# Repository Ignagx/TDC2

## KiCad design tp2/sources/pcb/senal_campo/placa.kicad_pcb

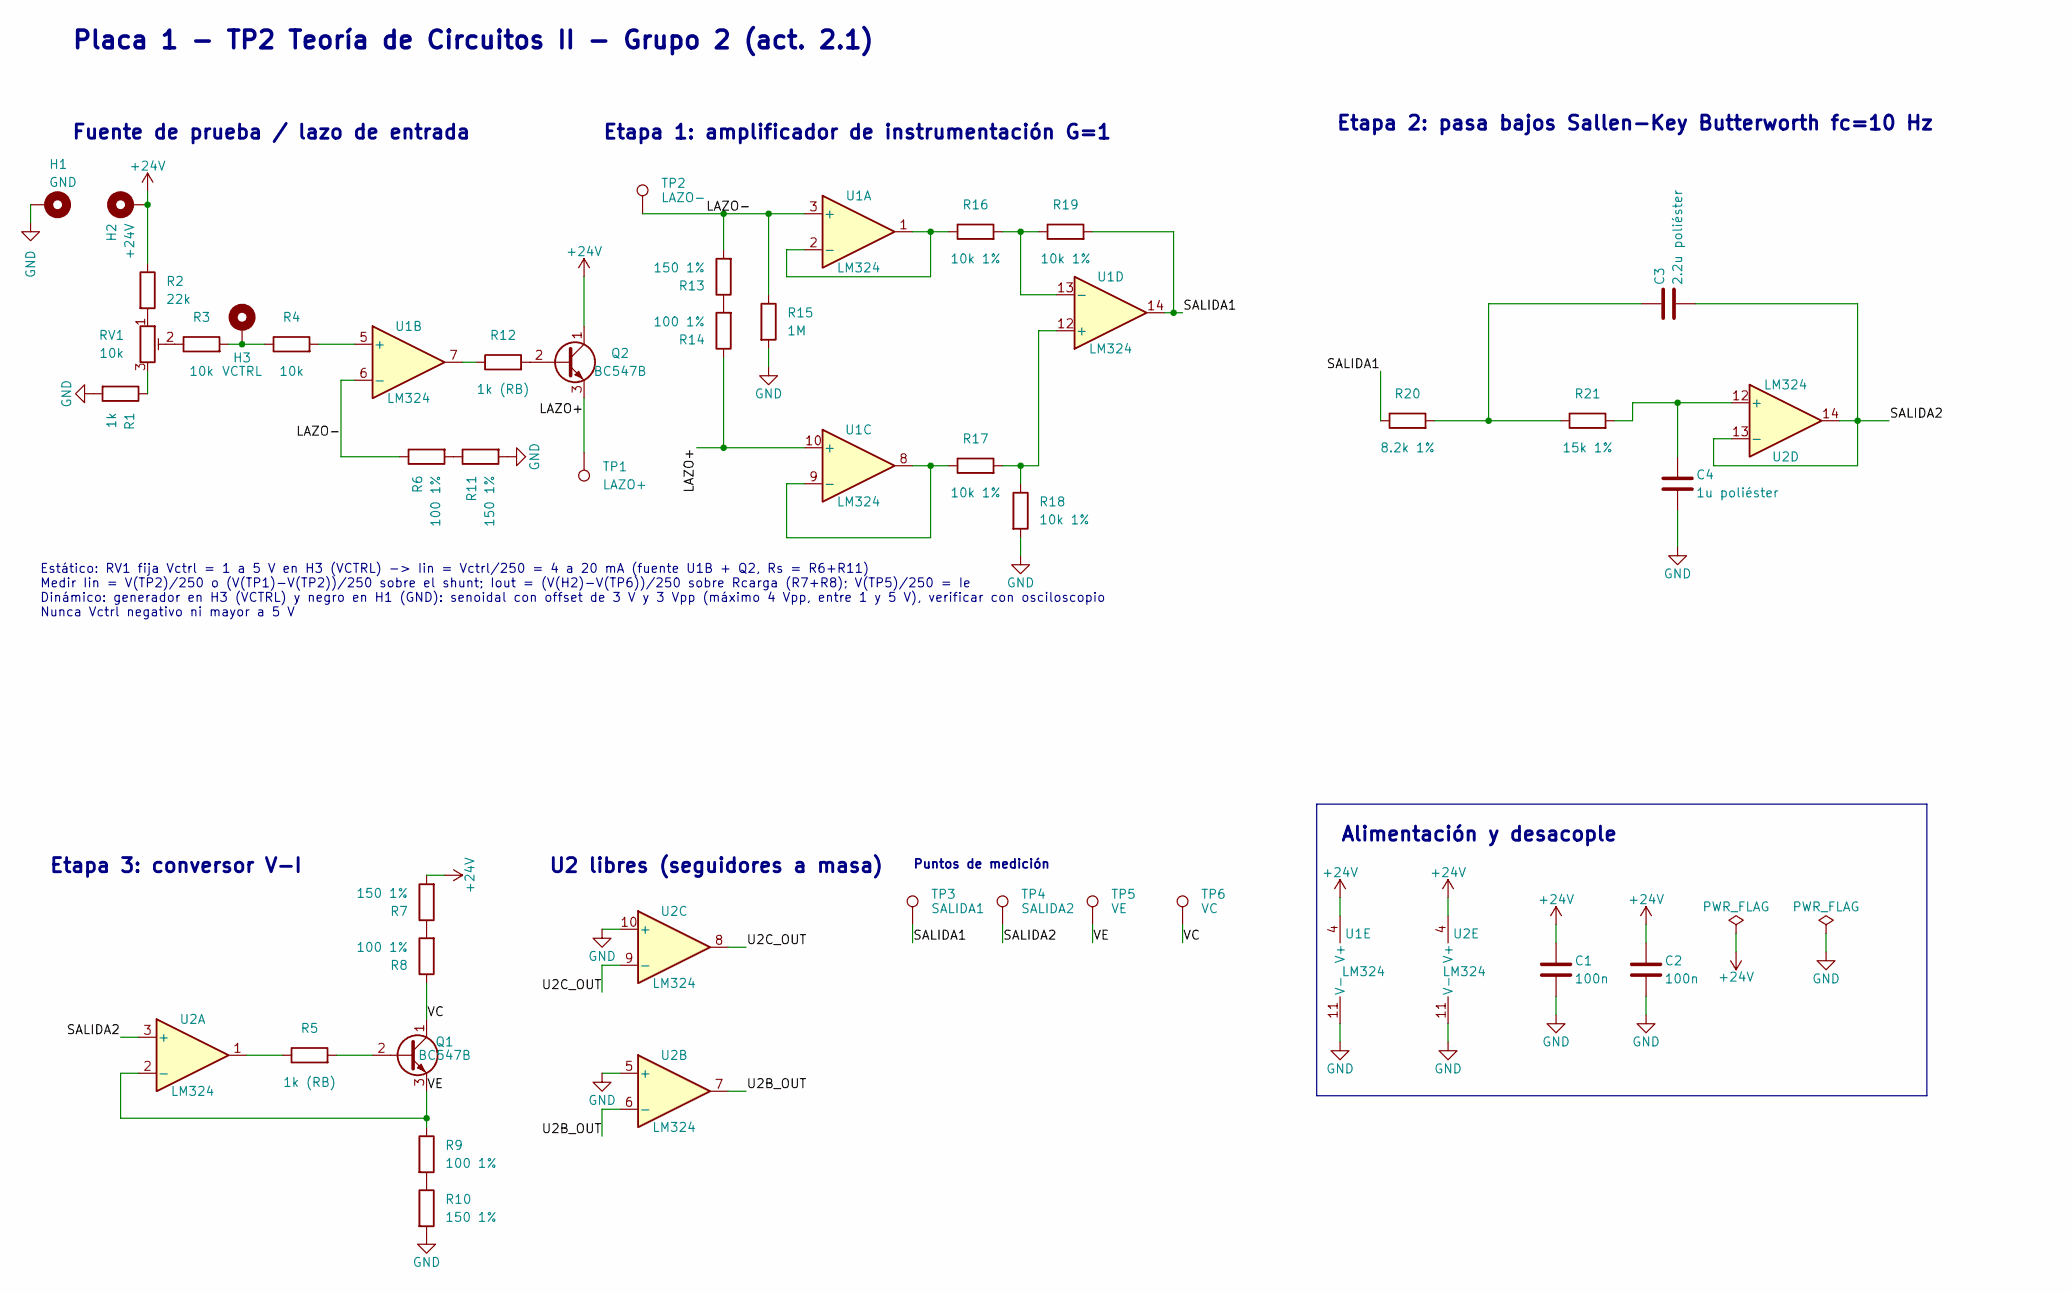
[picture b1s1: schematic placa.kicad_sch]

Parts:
C1, C2: 100n; C_Disc_D5.0mm_W2.5mm_P5.00mm
C3: 2.2u poliéster; C_Rect_L26.5mm_W10.5mm_P22.50mm_MKS4
C4: 1u poliéster; C_Rect_L7.2mm_W5.5mm_P5.00mm_FKS2_FKP2_MKS2_MKP2
H1: GND; Pad_Cocodrilo_6x8mm
H2: +24V; Pad_Cocodrilo_6x8mm
H3: VCTRL; Pad_Cocodrilo_6x8mm
Q1, Q2: BC547B; TO-92_Inline_Wide
R1: 1k; R_Axial_DIN0207_L6.3mm_D2.5mm_P10.16mm_Horizontal
R2: 22k; R_Axial_DIN0207_L6.3mm_D2.5mm_P10.16mm_Horizontal
R3, R4: 10k; R_Axial_DIN0207_L6.3mm_D2.5mm_P10.16mm_Horizontal
R5, R12: 1k (RB); R_Axial_DIN0207_L6.3mm_D2.5mm_P10.16mm_Horizontal
R6, R8, R9, R14: 100 1%; R_Axial_DIN0207_L6.3mm_D2.5mm_P10.16mm_Horizontal
R7, R10, R11, R13: 150 1%; R_Axial_DIN0207_L6.3mm_D2.5mm_P10.16mm_Horizontal
R15: 1M; R_Axial_DIN0207_L6.3mm_D2.5mm_P10.16mm_Horizontal
R16, R17, R18, R19: 10k 1%; R_Axial_DIN0207_L6.3mm_D2.5mm_P10.16mm_Horizontal
R20: 8.2k 1%; R_Axial_DIN0207_L6.3mm_D2.5mm_P10.16mm_Horizontal
R21: 15k 1%; R_Axial_DIN0207_L6.3mm_D2.5mm_P10.16mm_Horizontal
RV1: 10k; Potentiometer_Bourns_3296W_Vertical
TP1: LAZO+; TP_Puente_P5.08mm
TP2: LAZO-; TP_Puente_P5.08mm
TP3: SALIDA1; TP_Puente_P5.08mm
TP4: SALIDA2; TP_Puente_P5.08mm
TP5: VE; TP_Puente_P5.08mm
TP6: VC; TP_Puente_P5.08mm
U1, U2: LM324; DIP-14_W7.62mm_Socket

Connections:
+24V: C1.1, C2.1, H2.1, Q2.1 (C), R2.1, R7.2, U1.4 (V+), U2.4 (V+)
/LAZO+: Q2.3 (E), R14.1, TP1.1, U1.10 (+)
/LAZO-: R6.1, R13.2, R15.1, TP2.1, U1.3 (+), U1.6 (-)
/SALIDA1: R19.2, R20.1, TP3.1, U1.14
/SALIDA2: C3.2, TP4.1, U2.3 (+), U2.13 (-), U2.14
/U2B_OUT: U2.6 (-), U2.7
/U2C_OUT: U2.8, U2.9 (-)
/VC: Q1.1 (C), R8.1, TP6.1
/VE: Q1.3 (E), R9.1, TP5.1, U2.2 (-)
GND: C1.2, C2.2, C4.2, H1.1, R1.2, R10.2, R11.2, R15.2, R18.2, U1.11 (V-), U2.5 (+), U2.10 (+), U2.11 (V-)
unnamed: C3.1, R20.2, R21.1
unnamed: H3.1, R3.2, R4.1
unnamed: Q1.2 (B), R5.2
unnamed: Q2.2 (B), R12.2
unnamed: R1.1, RV1.3
unnamed: R2.2, RV1.1
unnamed: R3.1, RV1.2
unnamed: R5.1, U2.1
unnamed: R7.1, R8.2
unnamed: R9.2, R10.1
unnamed: R6.2, R11.1
unnamed: R12.1, U1.7
unnamed: R13.1, R14.2
unnamed: R16.1, U1.1, U1.2 (-)
unnamed: R4.2, U1.5 (+)
unnamed: R17.1, U1.8, U1.9 (-)
unnamed: R17.2, R18.1, U1.12 (+)
unnamed: R16.2, R19.1, U1.13 (-)
unnamed: C4.1, R21.2, U2.12 (+)

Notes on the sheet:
Placa 1 - TP2 Teoría de Circuitos II - Grupo 2 (act. 2.1)
Etapa 2: pasa bajos Sallen-Key Butterworth fc=10 Hz
Puntos de medición
Fuente de prueba / lazo de entrada
Etapa 3: conversor V-I
Estático: RV1 fija Vctrl = 1 a 5 V en H3 (VCTRL) -> Iin = Vctrl/250 = 4 a 20 mA (fuente U1B + Q2, Rs = R6+R11) Medir Iin = V(TP2)/250 o (V(TP1)-V(TP2))/250 sobre el shunt; Iout = (V(H2)-V(TP6))/250 sobre Rcarga (R7+R8); V(TP5)/250 = Ie Dinámico: generador en H3 (VCTRL) y negro en H1 (GND): senoidal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
Etapa 1: amplificador de instrumentación G=1
Alimentación y desacople
U2 libres (seguidores a masa)

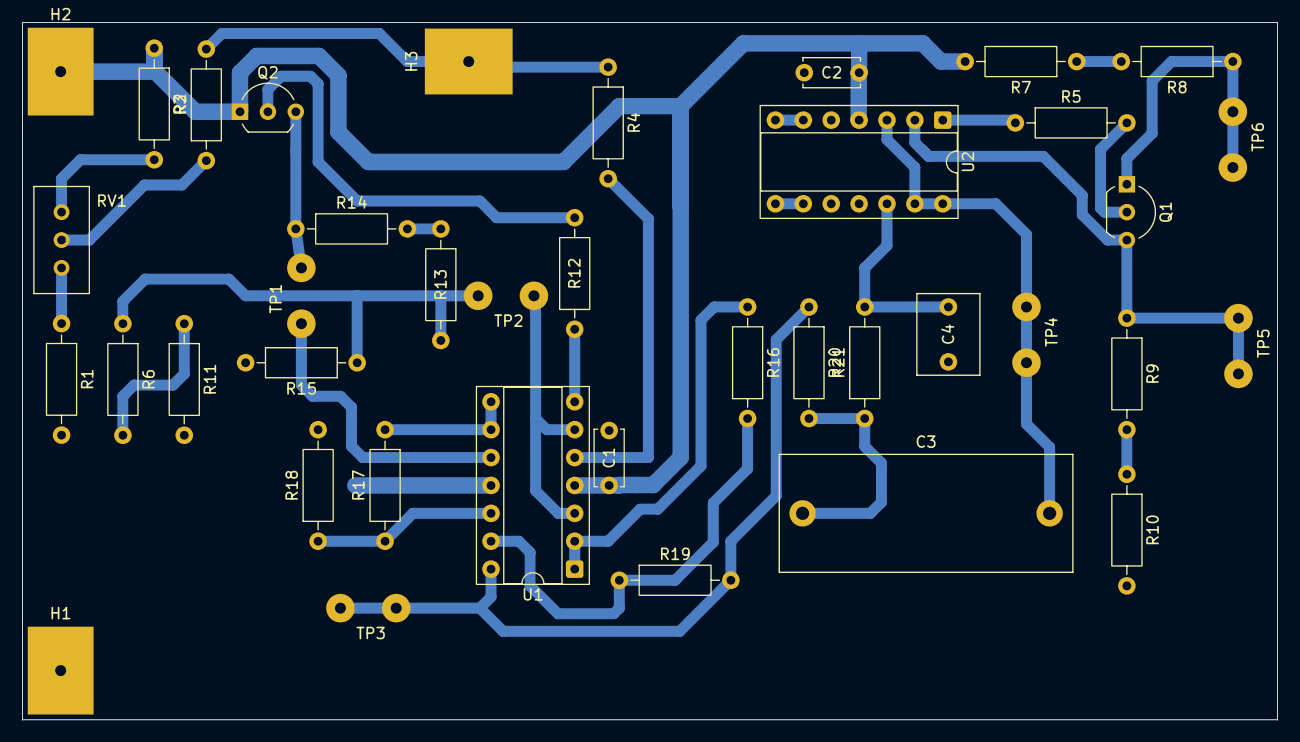
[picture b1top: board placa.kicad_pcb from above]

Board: 2 copper layers, 114.3 x 63.5 mm, 39 parts (0 on the bottom side), 29 nets.

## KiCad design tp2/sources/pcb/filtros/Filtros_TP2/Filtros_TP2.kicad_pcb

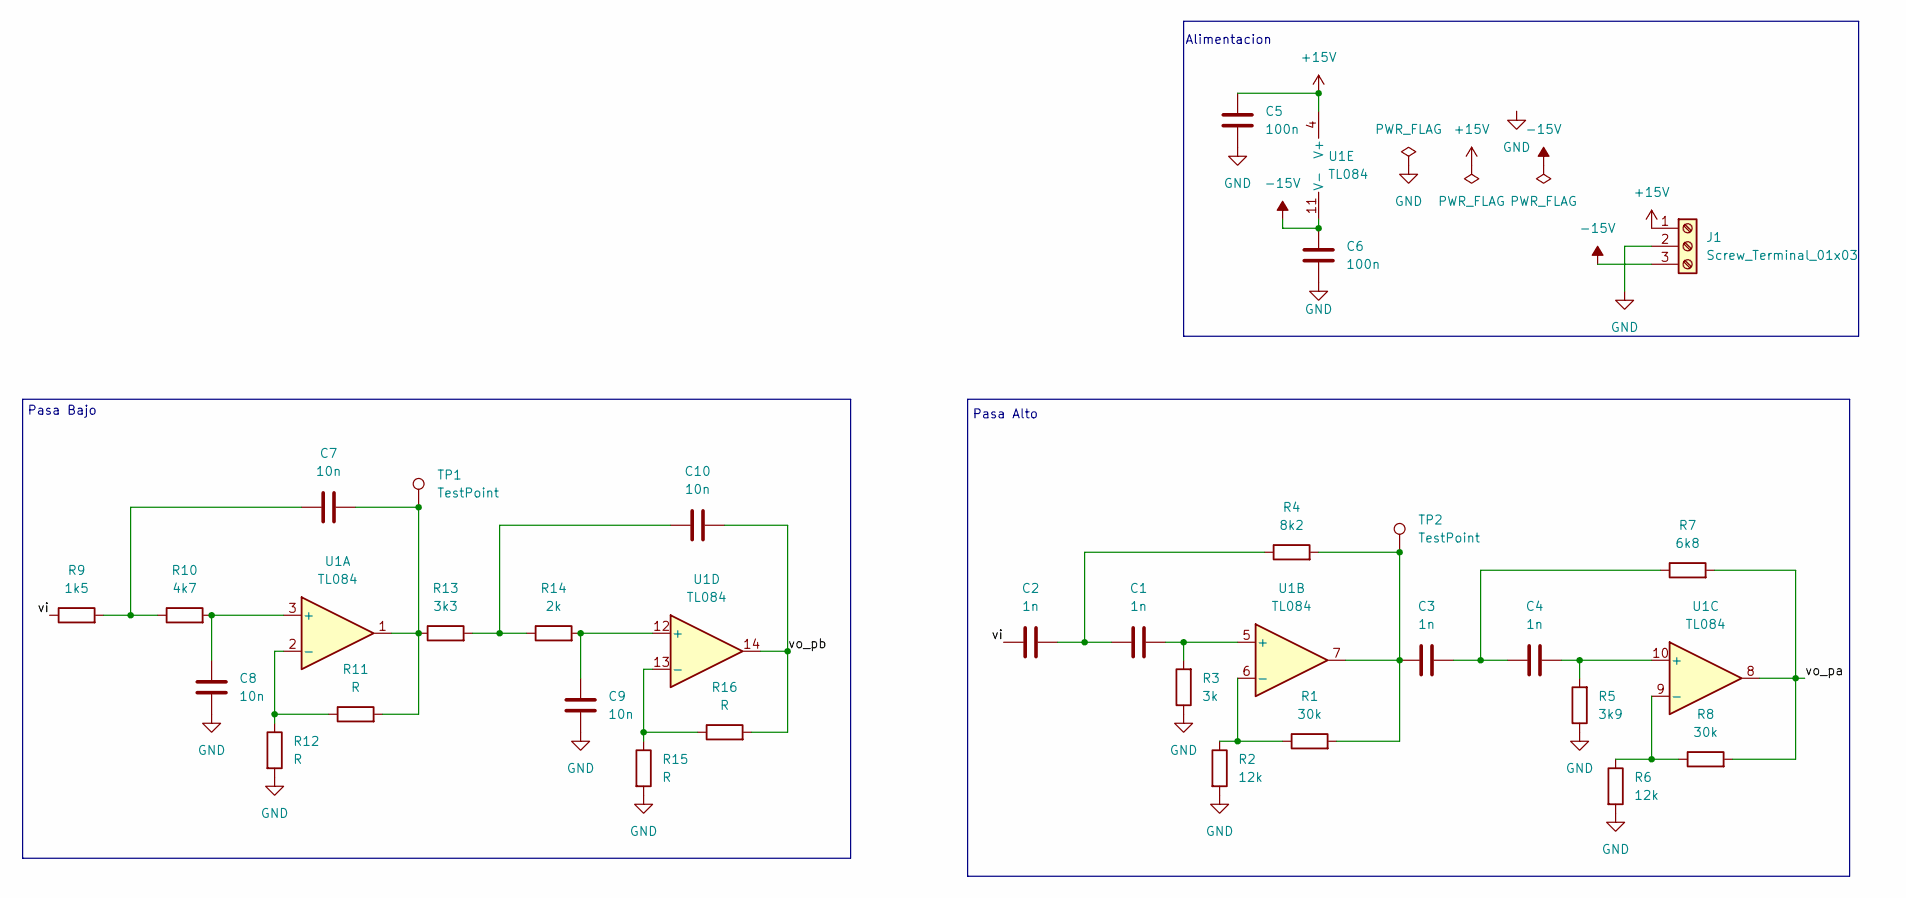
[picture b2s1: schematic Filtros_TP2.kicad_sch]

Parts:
C1, C2: 1n; C_Rect_L7.0mm_W2.5mm_P5.00mm
C3, C4: 1n; C_Disc_D5.0mm_W2.5mm_P5.00mm
C5, C6: 100n; C_Disc_D3.0mm_W1.6mm_P2.50mm
C7, C8, C9, C10: 10n; C_Rect_L7.0mm_W2.5mm_P5.00mm
J1: Screw_Terminal_01x03; TerminalBlock_MaiXu_MX126-5.0-03P_1x03_P5.00mm
R1, R8: 30k; R_Axial_DIN0207_L6.3mm_D2.5mm_P2.54mm_Vertical
R2: 12k; R_Axial_DIN0207_L6.3mm_D2.5mm_P2.54mm_Vertical
R3: 3k; R_Axial_DIN0207_L6.3mm_D2.5mm_P2.54mm_Vertical
R4: 8k2; R_Axial_DIN0207_L6.3mm_D2.5mm_P10.16mm_Horizontal
R5: 3k9; R_Axial_DIN0207_L6.3mm_D2.5mm_P2.54mm_Vertical
R6: 12k; R_Axial_DIN0207_L6.3mm_D2.5mm_P10.16mm_Horizontal
R7: 6k8; R_Axial_DIN0207_L6.3mm_D2.5mm_P2.54mm_Vertical
R9: 1k5; R_Axial_DIN0207_L6.3mm_D2.5mm_P10.16mm_Horizontal
R10: 4k7; R_Axial_DIN0207_L6.3mm_D2.5mm_P10.16mm_Horizontal
R11, R12, R15, R16: R; R_Axial_DIN0207_L6.3mm_D2.5mm_P2.54mm_Vertical
R13: 3k3; R_Axial_DIN0207_L6.3mm_D2.5mm_P10.16mm_Horizontal
R14: 2k; R_Axial_DIN0207_L6.3mm_D2.5mm_P10.16mm_Horizontal
TP1, TP2: TestPoint; PinHeader_1x02_P1.00mm_Vertical
U1: TL084; CERDIP-14_W7.62mm_SideBrazed_LongPads_Socket

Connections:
+15V: C5.1, J1.1, U1.4 (V+)
-15V: C6.1, J1.3, U1.11 (V-)
/vi: C2.1, R9.1
/vo_pa: R7.2, R8.2, U1.8
/vo_pb: C10.2, R16.2, U1.14
GND: C5.2, C6.2, C8.1, C9.1, J1.2, R2.2, R3.1, R5.1, R6.2, R12.2, R15.2
unnamed: C1.1, C2.2, R4.1
unnamed: C3.1, R1.2, R4.2, TP2.1 (1_1), U1.7
unnamed: C3.2, C4.1, R7.1
unnamed: C7.1, R9.2, R10.1
unnamed: C7.2, R11.2, R13.1, TP1.1 (1_1), U1.1
unnamed: C10.1, R13.2, R14.1
unnamed: C8.2, R10.2, U1.3 (+)
unnamed: R11.1, R12.1, U1.2 (-)
unnamed: C1.2, R3.2, U1.5 (+)
unnamed: R1.1, R2.1, U1.6 (-)
unnamed: C4.2, R5.2, U1.10 (+)
unnamed: R6.1, R8.1, U1.9 (-)
unnamed: C9.2, R14.2, U1.12 (+)
unnamed: R15.1, R16.1, U1.13 (-)

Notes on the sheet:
Pasa Alto
Alimentacion
Pasa Bajo

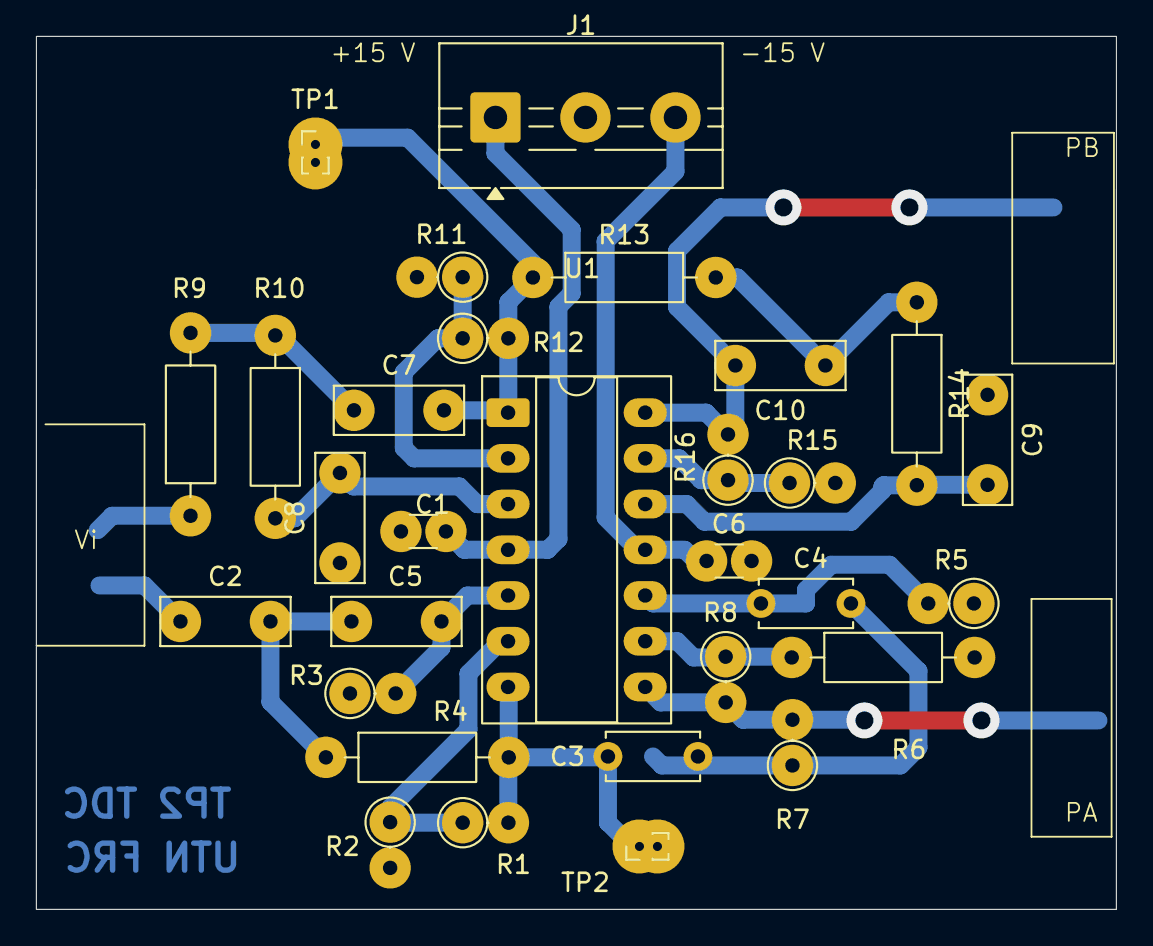
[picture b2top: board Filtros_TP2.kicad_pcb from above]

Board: 2 copper layers, 60.0 x 48.5 mm, 30 parts (0 on the bottom side), 20 nets.

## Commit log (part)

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2026-06-02 Inital commit
2026-06-02 Escribe script para la generacion de BODE
2026-06-02 Escribe script para graficos BODE circuito 2
2026-06-03 Corrige valor ideal del inductor
2026-06-08 Corrige valor de inductor en simulacion
2026-06-08 Agrega pdf's a gitignore
2026-06-08 Escribe introduccion
2026-06-08 Corrige gitignore para pdf
2026-06-08 Agrega los respectivos circuitos
2026-06-08 Agrega 2 circuitos en laplace
2026-06-08 Escribe primer desarrollo del circuito 1
2026-06-08 Agrega imagenes por python del circuito 1
2026-06-09 Avanza con la escritura del circuito 1
2026-06-10 Programa para bodes
2026-06-11 Formatea bode circt. 2
2026-06-14 Imagenes de los 3 ejercicios en el osciloscopio
2026-06-19 Update TP1 with Circuit 3 analysis and IEEEtran template adjustments
2026-06-19 Convert BMP to PNG, add author, remove TOC
2026-06-19 Update compiled PDF with PNG image and new author
2026-06-19 Forzar graficos con [H] y reajustar tamanios
2026-06-19 Fix layout overflows and minipages in circuit 1
2026-06-19 Fix pgfplots overlapping and undefined references
2026-06-19 Simulaciones ejercicio 3
2026-06-19 Add circuit 3 LTSpice simulation data
2026-06-19 Notas del lab parseadas a pdf
2026-06-19 Ajuste de formato y agregado de seccion Octave
2026-06-19 Ajustes finales: referencias en formato APA, capacitores C1/C2 y bodes act 3
2026-06-19 Completar analisis y graficos del circuito 2 y actualizar PDF
2026-06-21 Agrega diagramas de Bode (asintotico y simulacion) para el circuito 2
2026-06-22 Continua con el desarrollo del circuito 1
2026-06-23 Completar laboratorio del circuito 2 y agregar gráfico comparativo
2026-06-24 Ajuste de path de bodas y actualización del listado en el reporte
2026-06-24 Corregir label duplicado en circuito 1 y compilar PDF
2026-06-25 Termina circuito 1
2026-06-25 Modifica plots en circuito 2
2026-06-27 Corregir desborde de imagen en figura 8, resolver conflictos y compilar PDF final
2026-06-28 Unificar criterios de estilo de LaTeX, completar autores y renombrar archivo de salida a TDC2_TP1_4R2_Grupo2.pdf
